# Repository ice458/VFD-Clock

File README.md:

# VFD-Clock
This is a project for a table clock using a VFD.  
For more information, please visit [this site.](https://ice458.github.io/project-45472/)  

## License

The files contained in [VFD2.X/mcc_generated_files](VFD2.X/mcc_generated_files) are copyrighted by Microchip. The code can only be used in Microchip products. Please refer to the comments at the top of the files for details.

Other files are subject to the overall license [LICENSE](LICENSE).

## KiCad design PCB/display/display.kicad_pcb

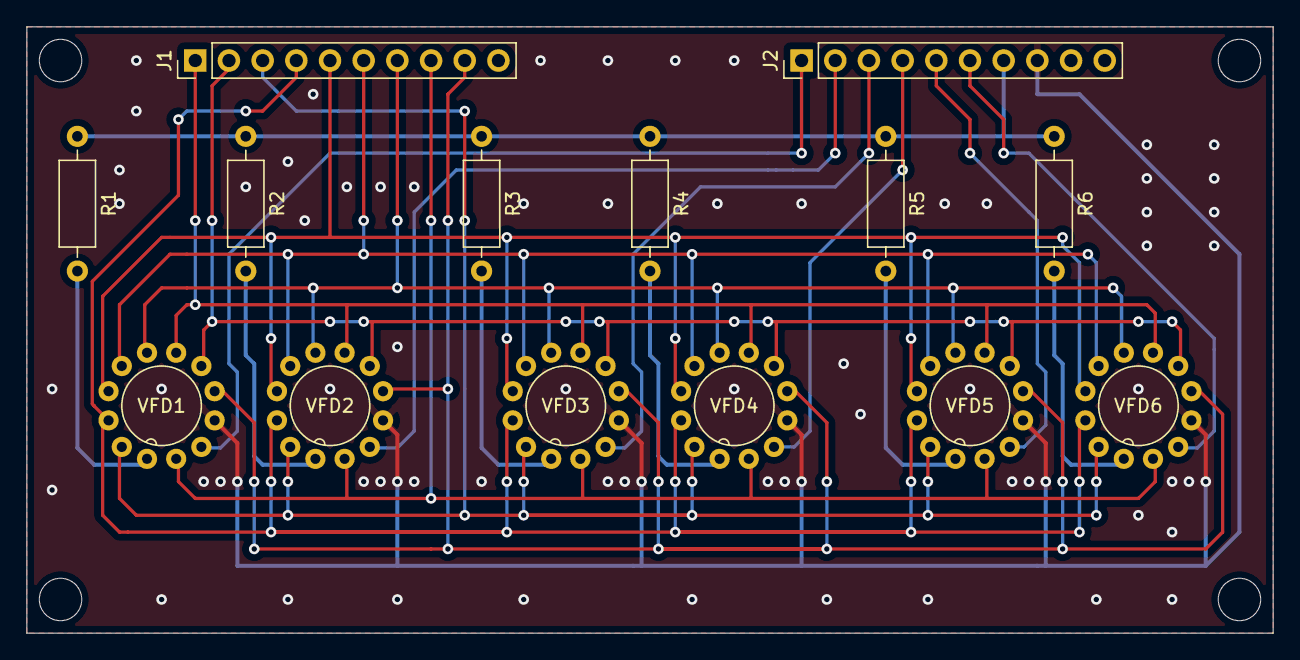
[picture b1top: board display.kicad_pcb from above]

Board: 2 copper layers, 94.0 x 45.7 mm, 14 parts (0 on the bottom side), 23 nets.

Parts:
J1, J2: Conn_01x10_Male; PinHeader_1x10_P2.54mm_Vertical
R1, R2, R3, R4, R5, R6: R; R_Axial_DIN0207_L6.3mm_D2.5mm_P10.16mm_Horizontal
VFD1, VFD2, VFD3, VFD4, VFD5, VFD6: LD8035

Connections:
+1V0: J2.7, R1.1, R2.1, R3.1, R4.1, R5.1, R6.1
/0: J2.1, VFD1.11
/1: J2.2, VFD2.11
/2: J2.3, VFD3.11
/3: J2.4, VFD4.11
/4: J2.5, VFD5.11
/5: J2.6, VFD6.11
/-: J1.9, VFD1.9, VFD2.9, VFD3.9, VFD4.9, VFD5.9, VFD6.9
/a: J1.1, VFD1.7, VFD2.7, VFD3.7, VFD4.7, VFD5.7, VFD6.7
/b: J1.2, VFD1.8, VFD2.8, VFD3.8, VFD4.8, VFD5.8, VFD6.8
/c: J1.3, VFD1.2, VFD2.2, VFD3.2, VFD4.2, VFD5.2, VFD6.2
/d: J1.4, VFD1.3, VFD2.3, VFD3.3, VFD4.3, VFD5.3, VFD6.3
/dp: J1.8, VFD1.12, VFD2.12, VFD3.12, VFD4.12, VFD5.12, VFD6.12
/e: J1.5, VFD1.4, VFD2.4, VFD3.4, VFD4.4, VFD5.4, VFD6.4
/f: J1.6, VFD1.5, VFD2.5, VFD3.5, VFD4.5, VFD5.5, VFD6.5
/g: J1.7, VFD1.6, VFD2.6, VFD3.6, VFD4.6, VFD5.6, VFD6.6
GND: J2.8, VFD1.10, VFD2.10, VFD3.10, VFD4.10, VFD5.10, VFD6.10
unnamed: R1.2, VFD1.1
unnamed: R2.2, VFD2.1
unnamed: R3.2, VFD3.1
unnamed: R4.2, VFD4.1
unnamed: R5.2, VFD5.1
unnamed: R6.2, VFD6.1

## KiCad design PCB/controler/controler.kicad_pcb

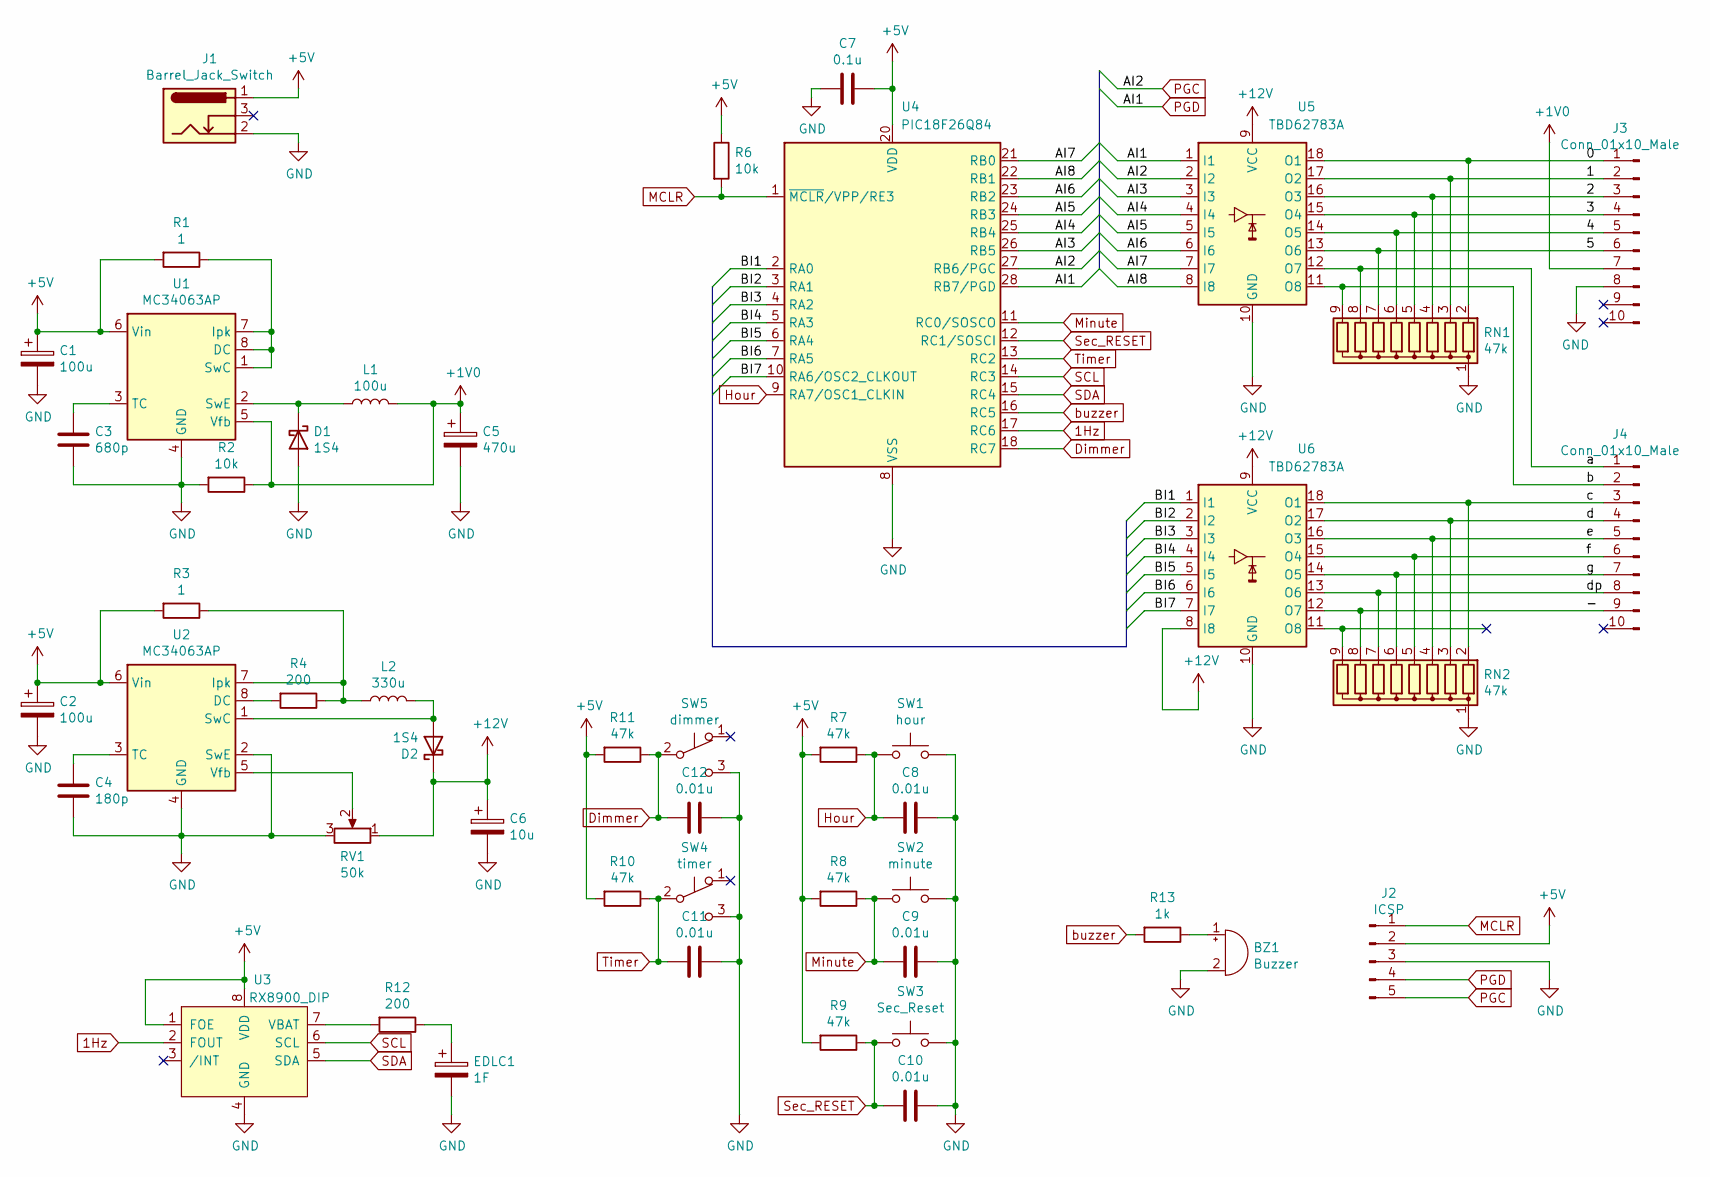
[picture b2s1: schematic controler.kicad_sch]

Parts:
BZ1: Buzzer; Buzzer_TDK_PS1240P02BT_D12.2mm_H6.5mm
C1, C2: 100u; CP_Radial_D6.3mm_P2.50mm
C3: 680p; C_Disc_D3.0mm_W1.6mm_P2.50mm
C4: 180p; C_Disc_D3.0mm_W1.6mm_P2.50mm
C5: 470u; CP_EIA-7343-30_AVX-N_Pad2.25x2.55mm_HandSolder
C6: 10u; CP_Radial_D5.0mm_P2.00mm
C7: 0.1u; C_0603_1608Metric_Pad1.08x0.95mm_HandSolder
C8, C9, C10, C11, C12: 0.01u; C_0603_1608Metric_Pad1.08x0.95mm_HandSolder
D1, D2: 1S4; D_DO-34_SOD68_P2.54mm_Vertical_AnodeUp
EDLC1: 1F; EDLC
J1: Barrel_Jack_Switch; BarrelJack_CUI_PJ-102AH_Horizontal
J2: ICSP; PinHeader_1x05_P2.54mm_Vertical
J3, J4: Conn_01x10_Male; PinHeader_1x10_P2.54mm_Vertical
L1: 100u; L_Axial_L9.5mm_D4.0mm_P12.70mm_Horizontal_Fastron_SMCC
L2: 330u; L_Axial_L9.5mm_D4.0mm_P12.70mm_Horizontal_Fastron_SMCC
R1, R3: 1; R_Axial_DIN0207_L6.3mm_D2.5mm_P10.16mm_Horizontal
R2, R6: 10k; R_Axial_DIN0207_L6.3mm_D2.5mm_P10.16mm_Horizontal
R4, R12: 200; R_Axial_DIN0207_L6.3mm_D2.5mm_P10.16mm_Horizontal
R7, R8, R9, R10, R11: 47k; R_Axial_DIN0207_L6.3mm_D2.5mm_P10.16mm_Horizontal
R13: 1k; R_Axial_DIN0207_L6.3mm_D2.5mm_P10.16mm_Horizontal
RN1, RN2: 47k; R_Array_SIP9
RV1: 50k; Potentiometer_Bourns_3386C_Horizontal
SW1: hour; R_Axial_DIN0204_L3.6mm_D1.6mm_P5.08mm_Horizontal
SW2: minute; R_Axial_DIN0204_L3.6mm_D1.6mm_P5.08mm_Horizontal
SW3: Sec_Reset; R_Axial_DIN0204_L3.6mm_D1.6mm_P5.08mm_Horizontal
SW4: timer; PinHeader_1x03_P2.54mm_Vertical
SW5: dimmer; PinHeader_1x03_P2.54mm_Vertical
U1, U2: MC34063AP; DIP-8_W7.62mm
U3: RX8900_DIP; DIP-8_Module_W7.62mm
U4: PIC18F26Q84; DIP-28_W7.62mm
U5, U6: TBD62783A; DIP-18_W7.62mm

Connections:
1Hz: U3.2 (FOUT), U4.17 (RC6)
+1V0: C5.1, J3.7, L1.2, R2.1, U1.5 (Vfb)
+5V: C1.1, C2.1, C7.1, J1.1, J2.2, R1.2, R3.2, R6.1, R7.2, R8.2, R9.2, R10.2, R11.2, U1.6 (Vin), U2.6 (Vin), U3.1 (FOE), U3.8 (VDD), U4.20 (VDD)
+12V: C6.1, D2.1 (K), RV1.1, U5.9 (VCC), U6.8 (I8), U6.9 (VCC)
/0: J3.1, RN1.2 (R1), U5.18 (O1)
/1: J3.2, RN1.3 (R2), U5.17 (O2)
/2: J3.3, RN1.4 (R3), U5.16 (O3)
/3: J3.4, RN1.5 (R4), U5.15 (O4)
/4: J3.5, RN1.6 (R5), U5.14 (O5)
/5: J3.6, RN1.7 (R6), U5.13 (O6)
/-: J4.9, RN2.8 (R7), U6.12 (O7)
/AI3: U4.26 (RB5), U5.3 (I3)
/AI4: U4.25 (RB4), U5.4 (I4)
/AI5: U4.24 (RB3), U5.5 (I5)
/AI6: U4.23 (RB2), U5.6 (I6)
/AI7: U4.21 (RB0), U5.7 (I7)
/AI8: U4.22 (RB1), U5.8 (I8)
/BI1: U4.2 (RA0), U6.1 (I1)
/BI2: U4.3 (RA1), U6.2 (I2)
/BI3: U4.4 (RA2), U6.3 (I3)
/BI4: U4.5 (RA3), U6.4 (I4)
/BI5: U4.6 (RA4), U6.5 (I5)
/BI6: U4.7 (RA5), U6.6 (I6)
/BI7: U4.10 (RA6/OSC2_CLKOUT), U6.7 (I7)
/a: J4.1, RN1.8 (R7), U5.12 (O7)
/b: J4.2, RN1.9 (R8), U5.11 (O8)
/c: J4.3, RN2.2 (R1), U6.18 (O1)
/d: J4.4, RN2.3 (R2), U6.17 (O2)
/dp: J4.8, RN2.7 (R6), U6.13 (O6)
/e: J4.5, RN2.4 (R3), U6.16 (O3)
/f: J4.6, RN2.5 (R4), U6.15 (O4)
/g: J4.7, RN2.6 (R5), U6.14 (O5)
Dimmer: C12.2, R11.1, SW5.2 (B), U4.18 (RC7)
GND: BZ1.2 (+), C1.2, C2.2, C3.2, C4.2, C5.2, C6.2, C7.2, C8.1, C9.1, C10.1, C11.1, C12.1, D1.2 (A), EDLC1.2, J1.2, J2.3, J3.8, R2.2, RN1.1 (common), RN2.1 (common), RV1.3, SW1.2, SW2.2, SW3.2, SW4.3 (C), SW5.3 (C), U1.4 (GND), U2.2 (SwE), U2.4 (GND), U3.4 (GND), U4.8 (VSS), U4.19 (VSS), U5.10 (GND), U6.10 (GND)
Hour: C8.2, R7.1, SW1.1, U4.9 (RA7/OSC1_CLKIN)
MCLR: J2.1, R6.2, U4.1 (~MCLR/VPP/RE3)
Minute: C9.2, R8.1, SW2.1, U4.11 (RC0/SOSCO)
unnamed: BZ1.1 (-), R13.1
unnamed: C3.1, U1.3 (TC)
unnamed: C4.1, U2.3 (TC)
unnamed: D1.1 (K), L1.1, U1.2 (SwE)
unnamed: D2.2 (A), L2.2, U2.1 (SwC)
unnamed: EDLC1.1, R12.1
unnamed: L2.1, R3.1, R4.1, U2.7 (Ipk)
unnamed: R1.1, U1.1 (SwC), U1.7 (Ipk), U1.8 (DC)
unnamed: R4.2, U2.8 (DC)
unnamed: R12.2, U3.7 (VBAT)
unnamed: RN2.9 (R8), U6.11 (O8)
unnamed: RV1.2, U2.5 (Vfb)
PGC: J2.5, U4.27 (RB6/PGC), U5.2 (I2)
PGD: J2.4, U4.28 (RB7/PGD), U5.1 (I1)
SCL: U3.6 (SCL), U4.14 (RC3)
SDA: U3.5 (SDA), U4.15 (RC4)
Sec_RESET: C10.2, R9.1, SW3.1, U4.12 (RC1/SOSCI)
Timer: C11.2, R10.1, SW4.2 (B), U4.13 (RC2)
buzzer: R13.2, U4.16 (RC5)

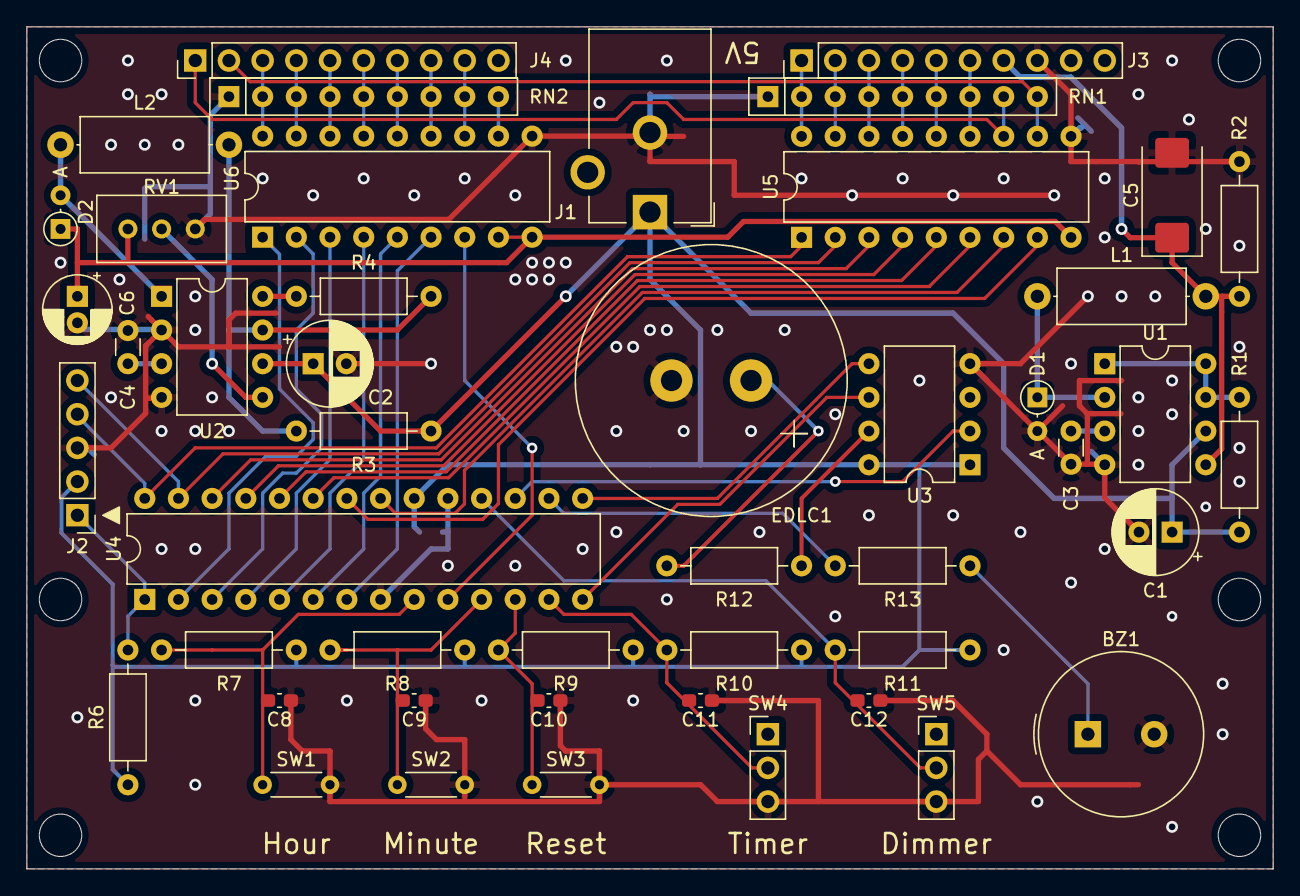
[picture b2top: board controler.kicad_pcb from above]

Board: 2 copper layers, 94.0 x 63.5 mm, 48 parts (1 on the bottom side), 56 nets.

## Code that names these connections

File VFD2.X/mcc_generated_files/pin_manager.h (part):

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// get/set Seg_C aliases
#define Seg_C_TRIS                 TRISAbits.TRISA0
#define Seg_C_LAT                  LATAbits.LATA0
#define Seg_C_PORT                 PORTAbits.RA0
#define Seg_C_WPU                  WPUAbits.WPUA0
#define Seg_C_OD                   ODCONAbits.ODCA0
#define Seg_C_ANS                  ANSELAbits.ANSELA0
#define Seg_C_SetHigh()            do { LATAbits.LATA0 = 1; } while(0)
#define Seg_C_SetLow()             do { LATAbits.LATA0 = 0; } while(0)
#define Seg_C_Toggle()             do { LATAbits.LATA0 = ~LATAbits.LATA0; } while(0)
#define Seg_C_GetValue()           PORTAbits.RA0
#define Seg_C_SetDigitalInput()    do { TRISAbits.TRISA0 = 1; } while(0)
#define Seg_C_SetDigitalOutput()   do { TRISAbits.TRISA0 = 0; } while(0)
#define Seg_C_SetPullup()          do { WPUAbits.WPUA0 = 1; } while(0)
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// get/set Seg_D aliases
#define Seg_D_TRIS                 TRISAbits.TRISA1
#define Seg_D_LAT                  LATAbits.LATA1
#define Seg_D_PORT                 PORTAbits.RA1
#define Seg_D_WPU                  WPUAbits.WPUA1
#define Seg_D_OD                   ODCONAbits.ODCA1
#define Seg_D_ANS                  ANSELAbits.ANSELA1
#define Seg_D_SetHigh()            do { LATAbits.LATA1 = 1; } while(0)
#define Seg_D_SetLow()             do { LATAbits.LATA1 = 0; } while(0)
#define Seg_D_Toggle()             do { LATAbits.LATA1 = ~LATAbits.LATA1; } while(0)
#define Seg_D_GetValue()           PORTAbits.RA1
#define Seg_D_SetDigitalInput()    do { TRISAbits.TRISA1 = 1; } while(0)
#define Seg_D_SetDigitalOutput()   do { TRISAbits.TRISA1 = 0; } while(0)
#define Seg_D_SetPullup()          do { WPUAbits.WPUA1 = 1; } while(0)
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// get/set Seg_E aliases
#define Seg_E_TRIS                 TRISAbits.TRISA2
#define Seg_E_LAT                  LATAbits.LATA2
#define Seg_E_PORT                 PORTAbits.RA2
#define Seg_E_WPU                  WPUAbits.WPUA2
#define Seg_E_OD                   ODCONAbits.ODCA2
#define Seg_E_ANS                  ANSELAbits.ANSELA2
#define Seg_E_SetHigh()            do { LATAbits.LATA2 = 1; } while(0)
#define Seg_E_SetLow()             do { LATAbits.LATA2 = 0; } while(0)
#define Seg_E_Toggle()             do { LATAbits.LATA2 = ~LATAbits.LATA2; } while(0)
#define Seg_E_GetValue()           PORTAbits.RA2
#define Seg_E_SetDigitalInput()    do { TRISAbits.TRISA2 = 1; } while(0)
#define Seg_E_SetDigitalOutput()   do { TRISAbits.TRISA2 = 0; } while(0)
#define Seg_E_SetPullup()          do { WPUAbits.WPUA2 = 1; } while(0)
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// get/set Seg_F aliases
#define Seg_F_TRIS                 TRISAbits.TRISA3
#define Seg_F_LAT                  LATAbits.LATA3
#define Seg_F_PORT                 PORTAbits.RA3
#define Seg_F_WPU                  WPUAbits.WPUA3
#define Seg_F_OD                   ODCONAbits.ODCA3
#define Seg_F_ANS                  ANSELAbits.ANSELA3
#define Seg_F_SetHigh()            do { LATAbits.LATA3 = 1; } while(0)
#define Seg_F_SetLow()             do { LATAbits.LATA3 = 0; } while(0)
#define Seg_F_Toggle()             do { LATAbits.LATA3 = ~LATAbits.LATA3; } while(0)
#define Seg_F_GetValue()           PORTAbits.RA3
#define Seg_F_SetDigitalInput()    do { TRISAbits.TRISA3 = 1; } while(0)
#define Seg_F_SetDigitalOutput()   do { TRISAbits.TRISA3 = 0; } while(0)
#define Seg_F_SetPullup()          do { WPUAbits.WPUA3 = 1; } while(0)
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// get/set Seg_G aliases
#define Seg_G_TRIS                 TRISAbits.TRISA4
#define Seg_G_LAT                  LATAbits.LATA4
#define Seg_G_PORT                 PORTAbits.RA4
#define Seg_G_WPU                  WPUAbits.WPUA4
#define Seg_G_OD                   ODCONAbits.ODCA4
#define Seg_G_ANS                  ANSELAbits.ANSELA4
#define Seg_G_SetHigh()            do { LATAbits.LATA4 = 1; } while(0)
#define Seg_G_SetLow()             do { LATAbits.LATA4 = 0; } while(0)
#define Seg_G_Toggle()             do { LATAbits.LATA4 = ~LATAbits.LATA4; } while(0)
#define Seg_G_GetValue()           PORTAbits.RA4
#define Seg_G_SetDigitalInput()    do { TRISAbits.TRISA4 = 1; } while(0)
#define Seg_G_SetDigitalOutput()   do { TRISAbits.TRISA4 = 0; } while(0)
#define Seg_G_SetPullup()          do { WPUAbits.WPUA4 = 1; } while(0)
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// get/set Seg_DP aliases
#define Seg_DP_TRIS                 TRISAbits.TRISA5
#define Seg_DP_LAT                  LATAbits.LATA5
#define Seg_DP_PORT                 PORTAbits.RA5
#define Seg_DP_WPU                  WPUAbits.WPUA5
#define Seg_DP_OD                   ODCONAbits.ODCA5
#define Seg_DP_ANS                  ANSELAbits.ANSELA5
#define Seg_DP_SetHigh()            do { LATAbits.LATA5 = 1; } while(0)
#define Seg_DP_SetLow()             do { LATAbits.LATA5 = 0; } while(0)
#define Seg_DP_Toggle()             do { LATAbits.LATA5 = ~LATAbits.LATA5; } while(0)
#define Seg_DP_GetValue()           PORTAbits.RA5
#define Seg_DP_SetDigitalInput()    do { TRISAbits.TRISA5 = 1; } while(0)
#define Seg_DP_SetDigitalOutput()   do { TRISAbits.TRISA5 = 0; } while(0)
#define Seg_DP_SetPullup()          do { WPUAbits.WPUA5 = 1; } while(0)
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// get/set Seg_Bar aliases
#define Seg_Bar_TRIS                 TRISAbits.TRISA6
#define Seg_Bar_LAT                  LATAbits.LATA6
#define Seg_Bar_PORT                 PORTAbits.RA6
#define Seg_Bar_WPU                  WPUAbits.WPUA6
#define Seg_Bar_OD                   ODCONAbits.ODCA6
#define Seg_Bar_ANS                  ANSELAbits.ANSELA6
#define Seg_Bar_SetHigh()            do { LATAbits.LATA6 = 1; } while(0)
#define Seg_Bar_SetLow()             do { LATAbits.LATA6 = 0; } while(0)
#define Seg_Bar_Toggle()             do { LATAbits.LATA6 = ~LATAbits.LATA6; } while(0)
#define Seg_Bar_GetValue()           PORTAbits.RA6
#define Seg_Bar_SetDigitalInput()    do { TRISAbits.TRISA6 = 1; } while(0)
#define Seg_Bar_SetDigitalOutput()   do { TRISAbits.TRISA6 = 0; } while(0)
#define Seg_Bar_SetPullup()          do { WPUAbits.WPUA6 = 1; } while(0)
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// get/set BTN_Hour aliases
#define BTN_Hour_TRIS                 TRISAbits.TRISA7
#define BTN_Hour_LAT                  LATAbits.LATA7
#define BTN_Hour_PORT                 PORTAbits.RA7
#define BTN_Hour_WPU                  WPUAbits.WPUA7
#define BTN_Hour_OD                   ODCONAbits.ODCA7
#define BTN_Hour_ANS                  ANSELAbits.ANSELA7
#define BTN_Hour_SetHigh()            do { LATAbits.LATA7 = 1; } while(0)
#define BTN_Hour_SetLow()             do { LATAbits.LATA7 = 0; } while(0)
#define BTN_Hour_Toggle()             do { LATAbits.LATA7 = ~LATAbits.LATA7; } while(0)
#define BTN_Hour_GetValue()           PORTAbits.RA7
#define BTN_Hour_SetDigitalInput()    do { TRISAbits.TRISA7 = 1; } while(0)
#define BTN_Hour_SetDigitalOutput()   do { TRISAbits.TRISA7 = 0; } while(0)
#define BTN_Hour_SetPullup()          do { WPUAbits.WPUA7 = 1; } while(0)
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// get/set Seg_A aliases
#define Seg_A_TRIS                 TRISBbits.TRISB0
#define Seg_A_LAT                  LATBbits.LATB0
#define Seg_A_PORT                 PORTBbits.RB0
#define Seg_A_WPU                  WPUBbits.WPUB0
#define Seg_A_OD                   ODCONBbits.ODCB0
#define Seg_A_ANS                  ANSELBbits.ANSELB0
#define Seg_A_SetHigh()            do { LATBbits.LATB0 = 1; } while(0)
#define Seg_A_SetLow()             do { LATBbits.LATB0 = 0; } while(0)
#define Seg_A_Toggle()             do { LATBbits.LATB0 = ~LATBbits.LATB0; } while(0)
#define Seg_A_GetValue()           PORTBbits.RB0
#define Seg_A_SetDigitalInput()    do { TRISBbits.TRISB0 = 1; } while(0)
#define Seg_A_SetDigitalOutput()   do { TRISBbits.TRISB0 = 0; } while(0)
#define Seg_A_SetPullup()          do { WPUBbits.WPUB0 = 1; } while(0)
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// get/set Seg_B aliases
#define Seg_B_TRIS                 TRISBbits.TRISB1
#define Seg_B_LAT                  LATBbits.LATB1
#define Seg_B_PORT                 PORTBbits.RB1
#define Seg_B_WPU                  WPUBbits.WPUB1
#define Seg_B_OD                   ODCONBbits.ODCB1
#define Seg_B_ANS                  ANSELBbits.ANSELB1
#define Seg_B_SetHigh()            do { LATBbits.LATB1 = 1; } while(0)
#define Seg_B_SetLow()             do { LATBbits.LATB1 = 0; } while(0)
#define Seg_B_Toggle()             do { LATBbits.LATB1 = ~LATBbits.LATB1; } while(0)
#define Seg_B_GetValue()           PORTBbits.RB1
#define Seg_B_SetDigitalInput()    do { TRISBbits.TRISB1 = 1; } while(0)
#define Seg_B_SetDigitalOutput()   do { TRISBbits.TRISB1 = 0; } while(0)
#define Seg_B_SetPullup()          do { WPUBbits.WPUB1 = 1; } while(0)
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// get/set Col_5 aliases
#define Col_5_TRIS                 TRISBbits.TRISB2
#define Col_5_LAT                  LATBbits.LATB2
#define Col_5_PORT                 PORTBbits.RB2
#define Col_5_WPU                  WPUBbits.WPUB2
#define Col_5_OD                   ODCONBbits.ODCB2
#define Col_5_ANS                  ANSELBbits.ANSELB2
#define Col_5_SetHigh()            do { LATBbits.LATB2 = 1; } while(0)
#define Col_5_SetLow()             do { LATBbits.LATB2 = 0; } while(0)
#define Col_5_Toggle()             do { LATBbits.LATB2 = ~LATBbits.LATB2; } while(0)
#define Col_5_GetValue()           PORTBbits.RB2
#define Col_5_SetDigitalInput()    do { TRISBbits.TRISB2 = 1; } while(0)
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

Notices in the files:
VFD2.X/mcc_generated_files/pin_manager.h:
(c) 2018 Microchip Technology Inc. and its subsidiaries.
